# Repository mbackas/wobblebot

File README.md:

# WobbleBot
WobbleBot is a highly dynamic robot, capable of balancing atop a 3" cylinder. Click on the picture for a demo video.

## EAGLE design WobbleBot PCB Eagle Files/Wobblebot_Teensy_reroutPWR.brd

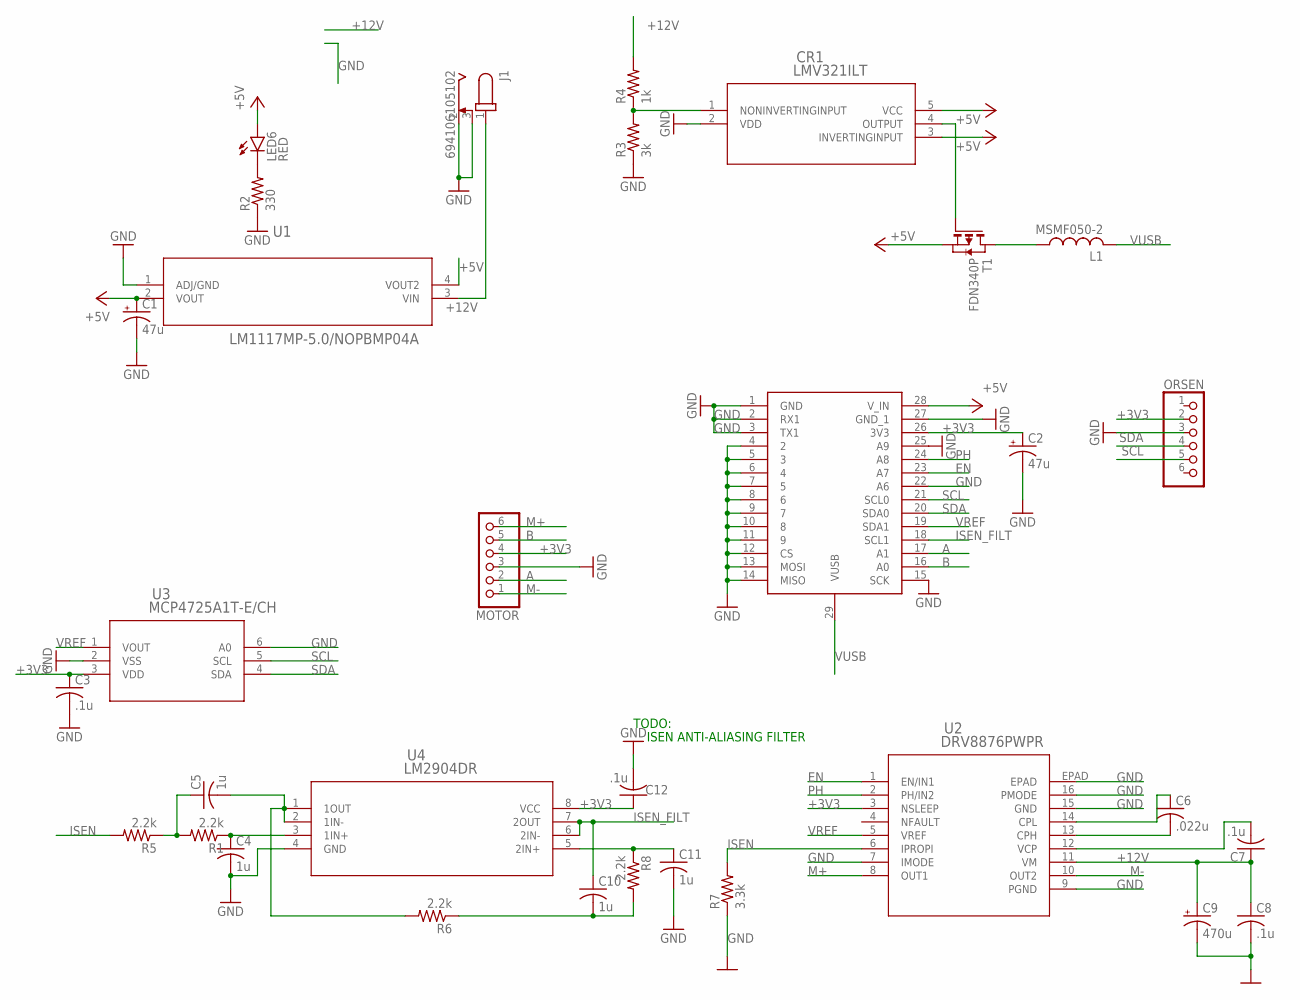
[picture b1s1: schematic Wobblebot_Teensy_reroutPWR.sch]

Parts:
C1, C2: 47u; 153CLV-0605
C3, C7, C8, C12: .1u; C0805
C4, C5, C10, C11: 1u; C0805
C6: .022u; C0805
C9: 470u; E5-10,5
CR1: LMV321ILT; SOT23-5
J1: 694106105102
L1: MSMF050-2; L1812
LED6: RED; CHIPLED_0805
MOTOR: PINHD-1X6; 1X06
ORSEN: PINHD-1X6; 1X06
R1, R5, R6, R8: 2.2k; R0805
R2: 330; R0805
R3: 3k; R0805
R4: 1k; R0805
R7: 3.3k; R0805
T1: FDN340P; SOT-23
U1: LM1117MP-5.0/NOPBMP04A; MP04A
U2: DRV8876PWPR; PWP16_2P31X2P46
U3: MCP4725A1T-E/CH; SOT-23-6_MC
U4: LM2904DR; D8
U$1: TEENSY4.0TEENSY4.0; DIP1524W53P254L3810H508Q28B

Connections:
+3V3: C2.+, C3.1, C12.1, MOTOR.4, ORSEN.2, U2.3 (NSLEEP), U3.3 (VDD), U4.8 (VCC), U$1.26 (3V3)
+5V: C1.+, CR1.3 (INVERTINGINPUT), CR1.5 (VCC), LED6.A, T1.2 (S), U1.2 (VOUT), U1.4 (VOUT2), U$1.28 (V_IN)
+12V: C7.1, C8.1, C9.+, J1.1, R4.2, U1.3 (VIN), U2.11 (VM)
A: MOTOR.2, U$1.17 (A1)
B: MOTOR.5, U$1.16 (A0)
EN: U2.1 (EN/IN1), U$1.23 (A7)
GND: C1.-, C2.-, C3.2, C4.2, C8.2, C9.-, C11.2, C12.2, CR1.2 (VDD), J1.2, J1.3, MOTOR.3, ORSEN.3, R2.1, R3.1, R7.1, U1.1 (ADJ/GND), U2.7 (IMODE), U2.9 (PGND), U2.15 (GND), U2.16 (PMODE), U2.EPAD, U3.2 (VSS), U3.6 (A0), U4.4 (GND), U$1.1 (GND), U$1.2 (RX1), U$1.3 (TX1), U$1.4 (2), U$1.5 (3), U$1.6 (4), U$1.7 (5), U$1.8 (6), U$1.9 (7), U$1.10 (8), U$1.11 (9), U$1.12 (CS), U$1.13 (MOSI), U$1.14 (MISO), U$1.15 (SCK), U$1.22 (A6), U$1.25 (A9), U$1.27 (GND_1)
ISEN: R5.2, R7.2, U2.6 (IPROPI)
ISEN_FILT: C10.1, U4.6 (2IN-), U4.7 (2OUT), U$1.18 (SCL1)
M+: MOTOR.6, U2.8 (OUT1)
M-: MOTOR.1, U2.10 (OUT2)
unnamed: C5.2, R6.2, U4.1 (1OUT), U4.2 (1IN-)
unnamed: CR1.1 (NONINVERTINGINPUT), R3.2, R4.1
unnamed: LED6.C, R2.2
unnamed: CR1.4 (OUTPUT), T1.3 (G)
unnamed: C11.1, R8.1, U4.5 (2IN+)
unnamed: C10.2, R6.1, R8.2
unnamed: C5.1, R1.2, R5.1
unnamed: C4.1, R1.1, U4.3 (1IN+)
unnamed: C6.1, U2.14 (CPL)
unnamed: C6.2, U2.13 (CPH)
unnamed: C7.2, U2.12 (VCP)
PH: U2.2 (PH/IN2), U$1.24 (A8)
SCL: ORSEN.5, U3.5 (SCL), U$1.21 (SCL0)
SDA: ORSEN.4, U3.4 (SDA), U$1.20 (SDA0)
USBVCC: L1.1, T1.1 (D)
VREF: U2.5 (VREF), U3.1 (VOUT), U$1.19 (SDA1)
VUSB: L1.2, U$1.29 (VUSB)

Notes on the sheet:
TODO:
ISEN ANTI-ALIASING FILTER

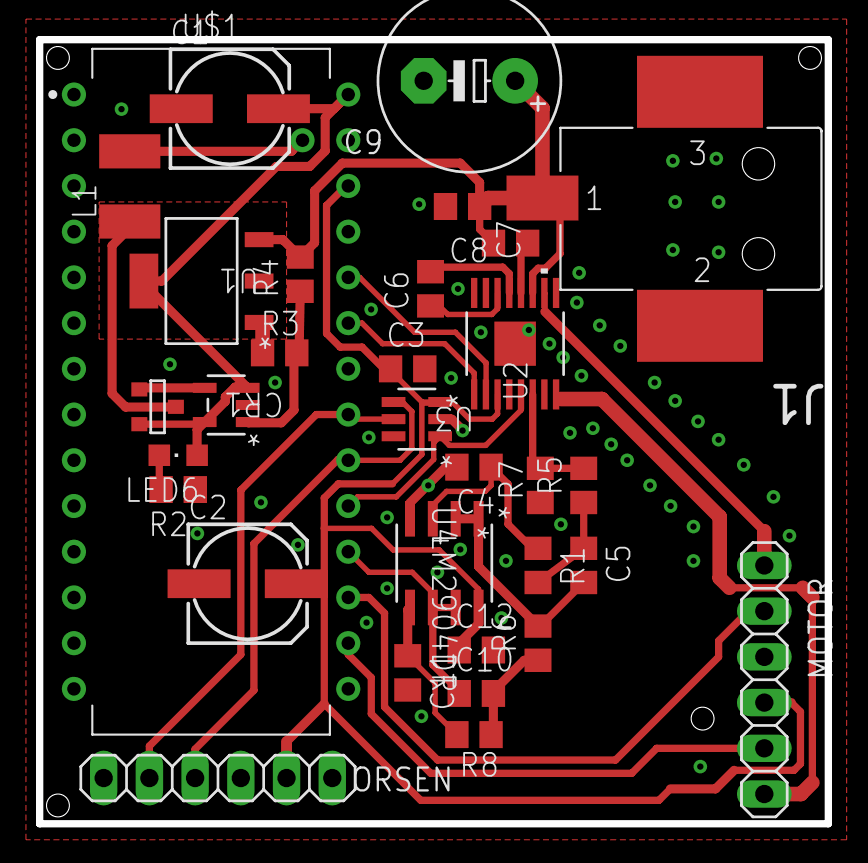
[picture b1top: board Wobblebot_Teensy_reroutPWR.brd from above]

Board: 2 copper layers, 43.8 x 43.6 mm, 32 parts (0 on the bottom side), 28 nets.

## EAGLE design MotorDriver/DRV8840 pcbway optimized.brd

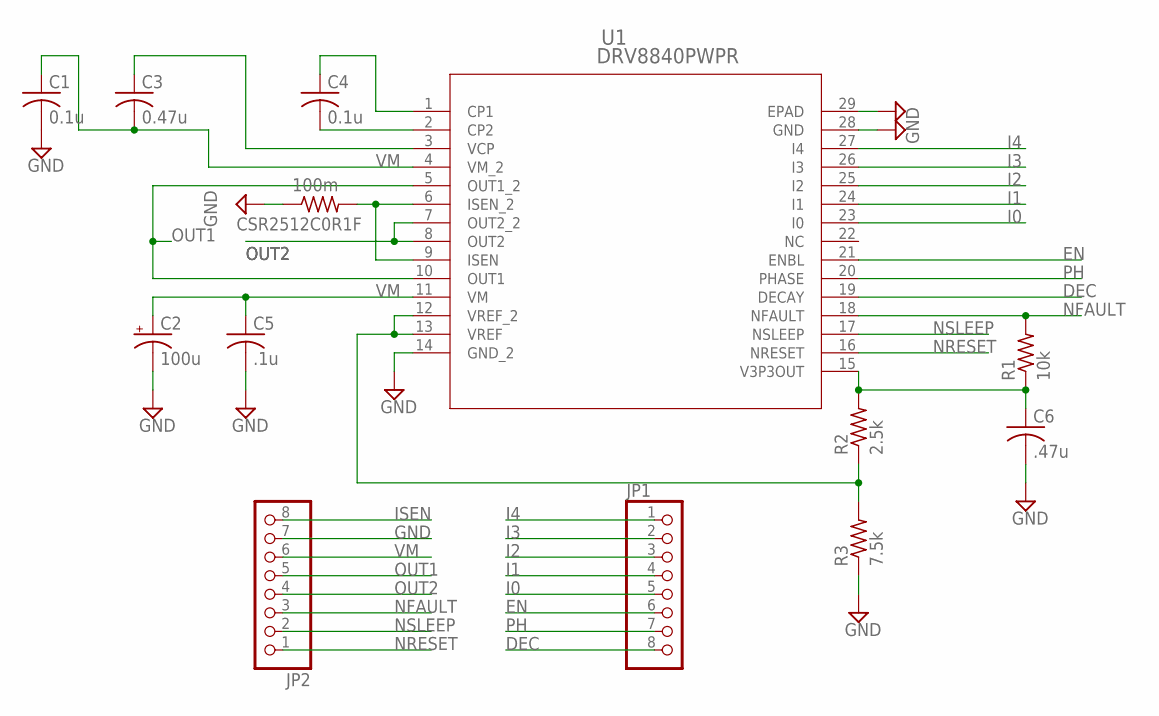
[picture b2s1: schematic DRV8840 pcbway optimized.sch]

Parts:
C1: 0.1u; C025-024X044
C2: 100u; E2,5-6
C3: 0.47u; C1206
C4: 0.1u; C1206
C5: .1u; C025-024X044
C6: .47u; C025-024X044
CSR2512C0R1F: 100m; R2512
JP1, JP2: PINHD-1X8; 1X08
R1: 10k; 0204V
R2: 2.5k; 0207/10
R3: 7.5k; 0207/10
U1: DRV8840PWPR; PWP28_5P18X3P1

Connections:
DEC: JP1.8, U1.19 (DECAY)
EN: JP1.6, U1.21 (ENBL)
GND: C1.2, C2.-, C5.2, C6.2, CSR2512C0R1F.1, JP2.7, R3.1, U1.14 (GND_2), U1.28 (GND), U1.29 (EPAD)
I0: JP1.5, U1.23 (I0)
I1: JP1.4, U1.24 (I1)
I2: JP1.3, U1.25 (I2)
I3: JP1.2, U1.26 (I3)
I4: JP1.1, U1.27 (I4)
ISEN: CSR2512C0R1F.2, JP2.8, U1.6 (ISEN_2), U1.9 (ISEN)
unnamed: C6.1, R1.1, R2.2, U1.15 (V3P3OUT)
unnamed: C4.2, U1.2 (CP2)
unnamed: C3.1, U1.3 (VCP)
unnamed: C4.1, U1.1 (CP1)
unnamed: R2.1, R3.2, U1.12 (VREF_2), U1.13 (VREF)
NFAULT: JP2.3, R1.2, U1.18 (NFAULT)
NRESET: JP2.1, U1.16 (NRESET)
NSLEEP: JP2.2, U1.17 (NSLEEP)
OUT1: JP2.5, U1.5 (OUT1_2), U1.10 (OUT1)
OUT2: JP2.4, U1.7 (OUT2_2), U1.8 (OUT2)
PH: JP1.7, U1.20 (PHASE)
VM: C1.1, C2.+, C3.2, C5.1, JP2.6, U1.4 (VM_2), U1.11 (VM)

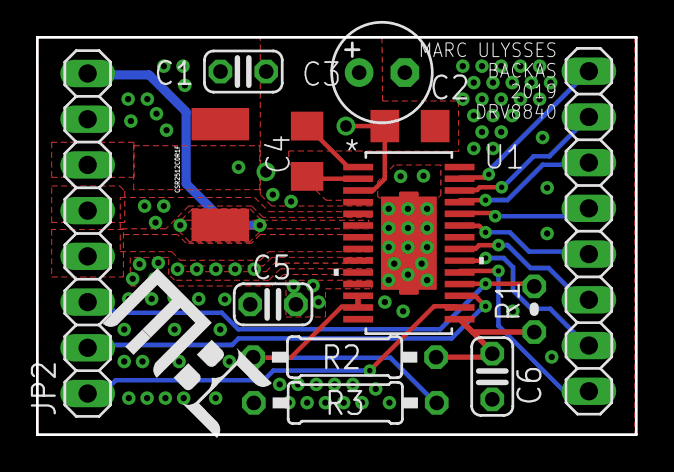
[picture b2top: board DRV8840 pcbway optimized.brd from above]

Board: 2 copper layers, 33.3 x 22.1 mm, 13 parts (0 on the bottom side), 21 nets.

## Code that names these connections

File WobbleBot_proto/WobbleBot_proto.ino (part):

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// measure another step, record the time elapsed. Calc. slope
//

# define nSLEEP 9
# define nRESET 5
# define I4 10
# define I3 11
# define I2 A2
# define I1 A1
# define I0 A0
# define ISEN A3
const int* current[5] = {I0, I1, I2, I3, I4};

# define EN 6
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
const double factor = 2.0 * 3.1415926 / 197.304;
void setup_pins() {
  pinMode(nSLEEP, OUTPUT);
  pinMode(nRESET, OUTPUT);
  pinMode(I4, OUTPUT);
  pinMode(I3, OUTPUT);
  pinMode(I2, OUTPUT);
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
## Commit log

2019-11-06 changed timer setup
2019-11-16 added backplane CAD files
2019-11-16 WobblebotBP.brd
2019-11-16 Latest MotorDriver CAD files. Hope to include variable vref next time with high res A/D
2019-11-16 fixed power source switching mechanism
2019-12-09 coppelia/vrep pythonClient code added
    run balance.py after loading wobbleBot.ttt in vrep
2019-12-09 wobblebot.ttt vrep scene added
2020-12-25 Added working Arduino project folder
2020-12-25 Added Eagle PCB files
    Anyone can make and assemble these pcbs using the .zip manufacturing files.
2021-04-19 updated MCU code to latest, work directly on this dir next time

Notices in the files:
parts and their libraries:
COPYRIGHT: Copyright (C) 2018 Accelerated Designs. All rights reserved
